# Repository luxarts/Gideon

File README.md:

## Acerca
El proyecto Otto consiste en el uso de inteligencia artificial para el intérprete de conversaciones de voz mediante servicios STT (Speech-To-Text) y TTS (Text-To-Speech). Cuenta con una interfaz web para su administración mediante el uso de servidores HTTP Apache y bases de datos MySQL. El hardware utilizado es una Raspberry Pi 3B, la cual se encarga de administrar tanto los servicios de voz, la captura de imagen, el servidor web y las bases de datos.

Toda la documentación es libre y gratuita bajo la licencia MIT y se puede encontrar en el repositorio de [GitHub](http://github.com/luxarts/Otto) y en la [Wiki](https://github.com/luxarts/Otto/wiki).

### Links útiles
- [Voice Command 3.0 (STT)](http://stevenhickson.blogspot.com.ar/2013/06/voice-command-v30-for-raspberry-pi.html)
- [eSpeak (TTS)](http://espeak.sourceforge.net)
  - [Solución errores ALSA](https://www.raspberrypi.org/forums/viewtopic.php?p=913285#p913285)
  - [Archivos de voz](http://espeak.sourceforge.net/voices.html)
- [Julius (STT)](https://github.com/julius-speech/julius)
  - [Modelos de lenguaje](https://www.raspberrypi.org/forums/viewtopic.php?f=76&t=105867)
  - [Tutorial Rasperry Pi](https://www.raspberrypi.org/forums/viewtopic.php?p=1032201#p1032201)
- [Hotspot WIFI automático](http://www.raspberryconnect.com/network/item/315-rpi3-auto-wifi-hotspot-if-no-internet)
- [Raspbian](https://www.raspberrypi.org/downloads/raspbian/)
- [Argumentos en scripts de Python](https://www.cyberciti.biz/faq/python-command-line-arguments-argv-example/)
- [Script de Python ejecutable](https://www.modmypi.com/blog/how-to-make-python-programs-executable)
- [Ejecutar comando en segundo plano](http://raultomas.me/ejecucion-de-comandos-en-segundo-plano-sobre-linux/)
- [Conexión a MySQL a través de Python](http://stackoverflow.com/a/622308)
  - [Info sobre MySQLdb](https://www.python.org/dev/peps/pep-0249/)

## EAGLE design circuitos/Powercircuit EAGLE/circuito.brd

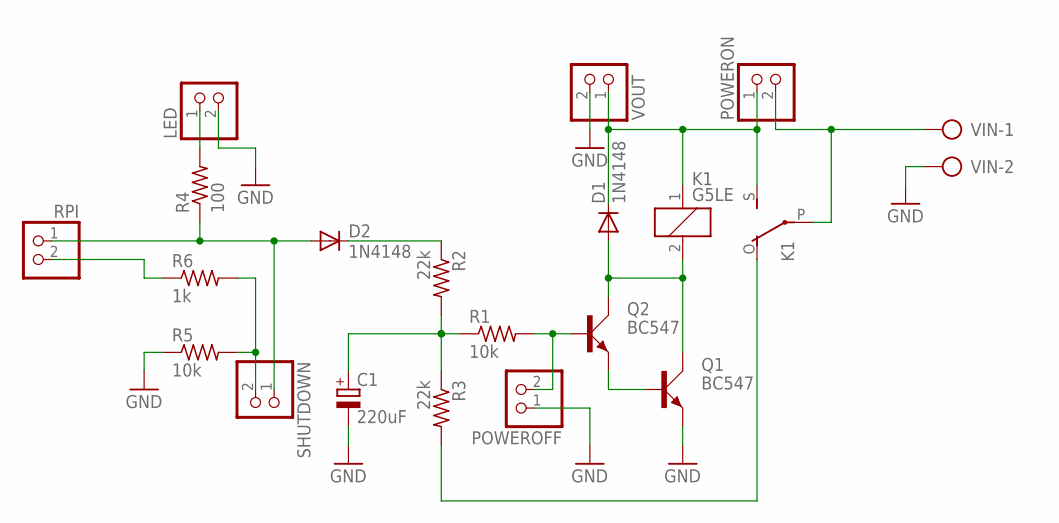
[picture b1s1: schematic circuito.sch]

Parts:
C1: 220uF; E2,5-6E
D1, D2: 1N4148; DO35-7
K1: G5LE
LED: PINHD-1X2; 1X02
POWEROFF: PINHD-1X2; 1X02
POWERON: PINHD-1X2; 1X02
Q1, Q2: BC547; SOT54A
R1, R5: 10k; 0207/7
R2, R3: 22k; 0207/7
R4: 100; 0207/7
R6: 1k; 0207/7
RPI: PINHD-1X2; 1X02
SHUTDOWN: PINHD-1X2; 1X02
VIN: AK500/2-H
VOUT: PINHD-1X2; 1X02

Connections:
GND: C1.-, LED.2, POWEROFF.1, Q1.E, R5.1, VIN.2, VOUT.2
unnamed: C1.+, R1.1, R2.2, R3.1
unnamed: D1.C, K1.1, K1.S, POWERON.1, VOUT.1
unnamed: Q1.B, Q2.E
unnamed: D1.A, K1.2, Q1.C, Q2.C
unnamed: K1.P, POWERON.2, VIN.1
unnamed: POWEROFF.2, Q2.B, R1.2
unnamed: D2.C, R2.1
unnamed: D2.A, R4.1, RPI.1, SHUTDOWN.1
unnamed: K1.O, R3.2
unnamed: LED.1, R4.2
unnamed: R6.1, RPI.2
unnamed: R5.2, R6.2, SHUTDOWN.2

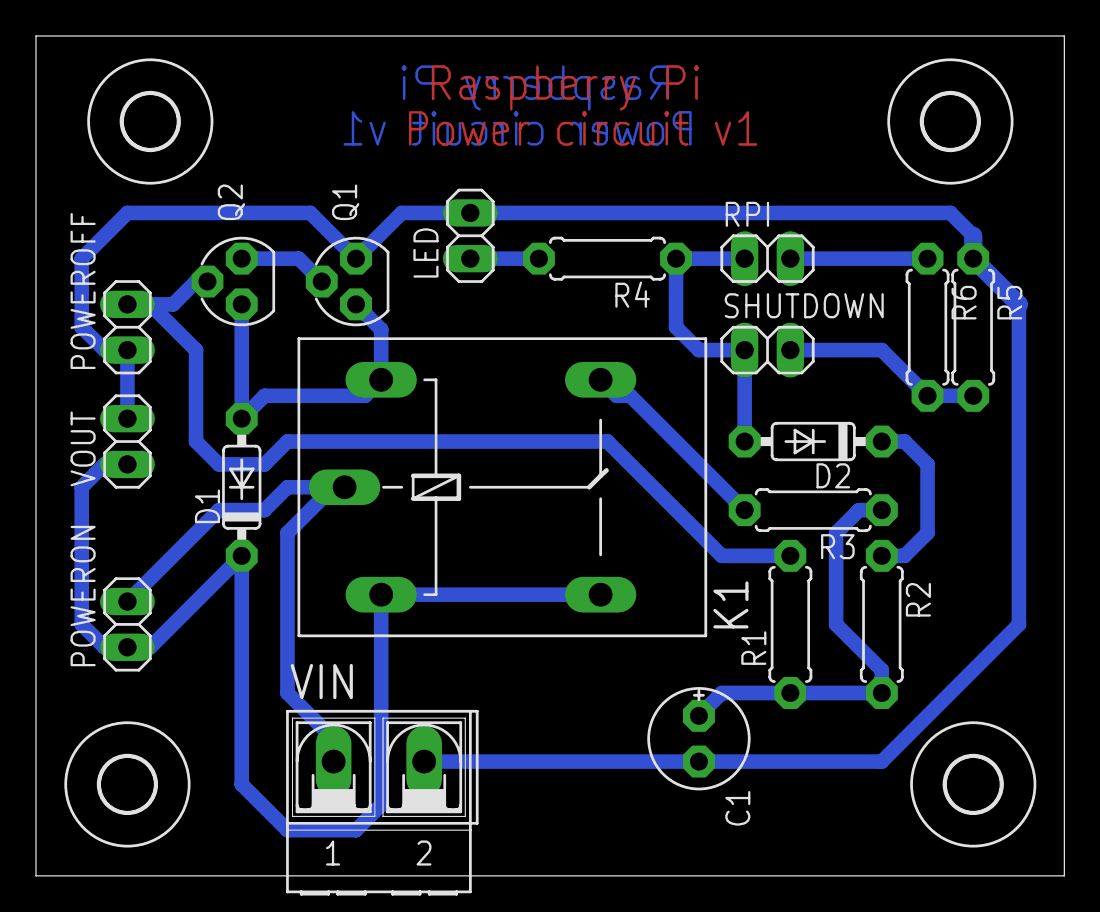
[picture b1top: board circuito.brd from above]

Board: 2 copper layers, 57.1 x 46.7 mm, 23 parts (0 on the bottom side), 13 nets.

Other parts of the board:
U$1, U$2, U$3, U$4: 3,0

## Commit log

2017-03-17 Set theme jekyll-theme-hacker
2017-04-08 Webpage
2017-04-08 Create python_scripts
